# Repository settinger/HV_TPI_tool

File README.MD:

# High-Voltage Tiny Programming Interface (HVTPI) Tool

For an upcoming project I needed a way to use the High-Voltage Tiny Programming Interface (HVTPI) protocol. If you're at all familiar with the High-Voltage Serial Programming (HVSP) that can be used on most ATmegas and ATtinys that use the SPI protocol, then you would be justified to assume HVTPI is a convoluted process dissimilar from standard TPI. But, mercifully, that is not the case! HVTPI is just TPI, but instead of pulling the <span style="text-decoration:overline">RESET</span> pin LOW, you pull it up to 12V.

Two low-cost options for TPI programming are the [USBasp](https://www.fischl.de/usbasp/) (with the [latest firmware](https://blog.podkalicki.com/how-to-update-avr-usbasp-firmware-to-latest-version/)) or the [TPI Programming Arduino Sketch](http://junkplusarduino.blogspot.com/p/attiny10-resources.html) by Junk+Arduino and others. Neither the USBasp nor the Arduino has a pin available to output 12V, of course. That requires some extra hardware.

The task is easy to summarize. Create a new signal that produces 5V when <span style="text-decoration:overline">RESET</span> produces 5V, and goes to 12V when <span style="text-decoration:overline">RESET</span> goes to 0V. On YouTube, [fVripple made a very good one with an optoisolator and a benchtop power supply](https://www.youtube.com/watch?v=7YJOtHbnNDQ), but I wanted to stick to parts I had on-hand and make it more portable. This is what I came up with:

An AP3012 boost converter gives us 12V all the time. While <span style="text-decoration:overline">RESET</span> is HIGH, the forward voltage of the Zener diode is high enough that no current flows through the PNP BJT and the output is equal to <span style="text-decoration:overline">RESET</span>. When <span style="text-decoration:overline">RESET</span> goes LOW, current flows through the 9.1V Zener diode, driving the output to 12V. The 5kΩ resistor value is not a precise one; I think I used 3.3kΩ in practice. And I broke out the 12V signal in case I ever wanted to use it for something else, I dunno what though.

To actually use this schematic, I made two designs: one to go with the USBasp and one to go with the Arduino TPI programmer. I was very sleep-deprived and made some silly design choices.

## The USBasp HVTPI tool

The USBasp HVTPI tool mates nicely with its 2×5 IDC headers. There are two SPDT switches, one to switch between normal TPI and HVTPI modes, and another to combine the two data lines as described in [this application note](http://ww1.microchip.com/downloads/en/AppNotes/doc8373.pdf):

These resistors are not always necessary, which is why they can be disconnected with the switch. The USBasp expects a circuit with a programming pinout like this:

Consequently, the line that is normally labelled "MOSI" acts as the bidirectional line when the USBasp does TPI stuff. This becomes a problem if you are using a circuit that was designed for the [Atmel-ICE](https://ww1.microchip.com/downloads/en/DeviceDoc/Atmel-ICE_UserGuide.pdf), which expects a programming pinout like this:

Both configurations are handled equally well by the 220Ω-resistor switch.

Using the HVTPI tool is as easy as normal TPI. As far as your computer is concerned, there is no difference between this and a normal TPI setup, so no instructions or makefiles have to change.

## The Arduino HVTPI tool

The Arduino-compatible programmer is designed to sit in a breadboard. I originally designed it very skinny, with the HVRST line sticking up like so:

This is not very helpful, so later I went back and put it in a more reasonable 10-DIP layout. Because the Arduino program expects both MISO and MOSI lines to connect to the TPI DATA line via 220Ω resistors, I built that into this board as well. Again, there is no need to make any changes to the normal TPI programming workflow. I know the Arduino sketch has some "HVP" options available, but with this board they are wholly unnecessary.

I'm happily using these with both the USBasp and the Arduino for HVTPI programming. I had a hard time finding good resources for HVTPI and had to do a lot of learning-by-doing, but hopefully I can pass that knowledge along and save someone some trouble.

# Note to self

After setting the ATtiny4/5/9/10/20/40 fuse bits to `0xFE` (or whatever) to enable 12V reset, avrdude can't just overwrite the fuses with `0xFF`. Using the flags `-x section_config -e` will clear the bits.

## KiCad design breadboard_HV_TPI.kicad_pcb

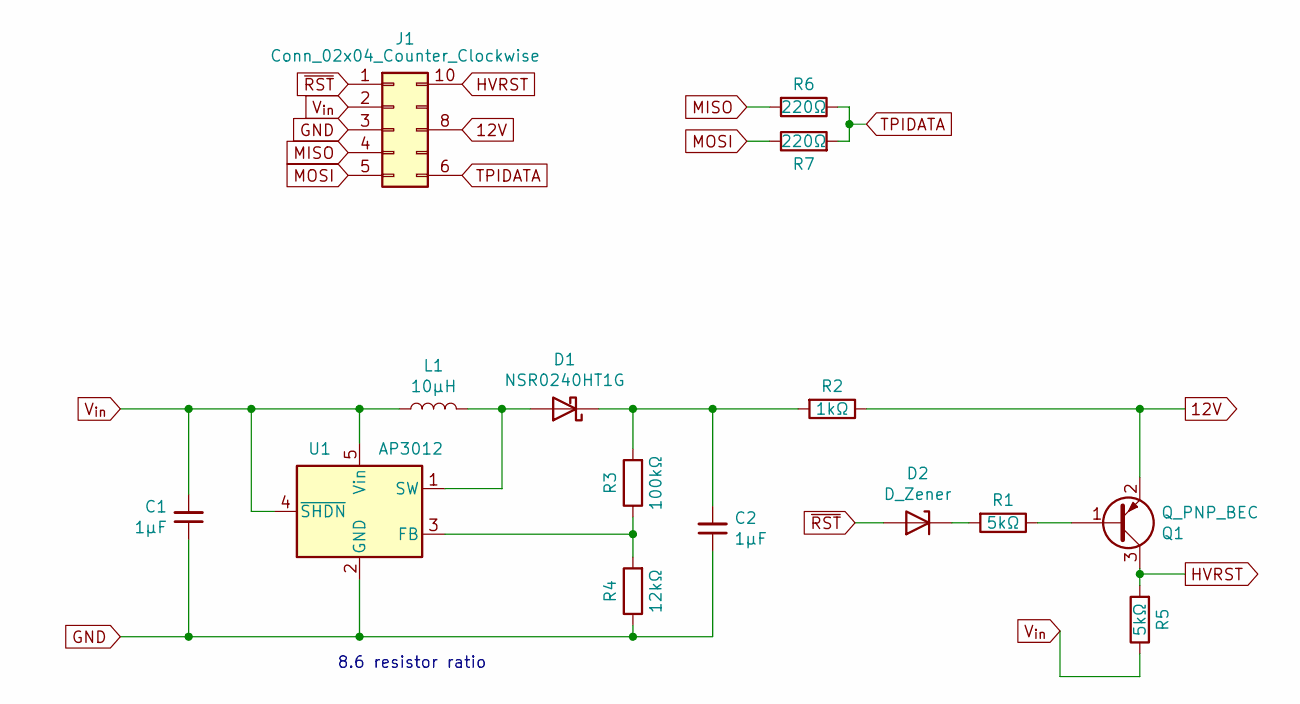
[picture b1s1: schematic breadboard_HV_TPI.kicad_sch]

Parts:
C1, C2: 1μF; C_0805_2012Metric
D1: NSR0240HT1G; D_SOD-323
D2: D_Zener; D_MiniMELF
J1: Conn_02x04_Counter_Clockwise; DIP-10_W7.62mm
L1: 10μH; L_0805_2012Metric
Q1: Q_PNP_BEC; SOT-23
R1, R5: 5kΩ; R_0805_2012Metric
R2: 1kΩ; R_0805_2012Metric
R3: 100kΩ; R_0805_2012Metric
R4: 12kΩ; R_0805_2012Metric
R6, R7: 220Ω; R_0805_2012Metric
U1: AP3012; SOT-23-5

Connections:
12V: J1.8, Q1.2 (E), R2.1
GND: C1.1, C2.1, J1.3, R4.1, U1.2 (GND)
HVRST: J1.10, Q1.3 (C), R5.2
MISO: J1.4, R6.2
MOSI: J1.5, R7.1
unnamed: C2.2, D1.1 (K), R2.2, R3.2
unnamed: D1.2 (A), L1.2, U1.1 (SW)
unnamed: D2.1 (K), R1.2
unnamed: Q1.1 (B), R1.1
unnamed: R3.1, R4.2, U1.3 (FB)
TPIDATA: J1.6, R6.1, R7.2
V_{in}: C1.2, J1.2, L1.1, R5.1, U1.4 (~SHDN), U1.5 (Vin)
~RST: D2.2 (A), J1.1

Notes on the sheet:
8.6 resistor ratio

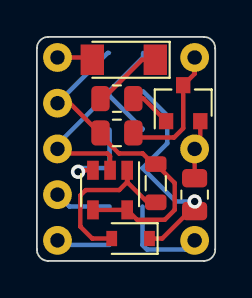
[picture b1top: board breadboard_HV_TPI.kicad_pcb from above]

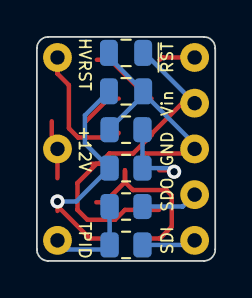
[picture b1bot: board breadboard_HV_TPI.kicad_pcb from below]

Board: 2 copper layers, 9.9 x 12.4 mm, 15 parts (6 on the bottom side), 13 nets.

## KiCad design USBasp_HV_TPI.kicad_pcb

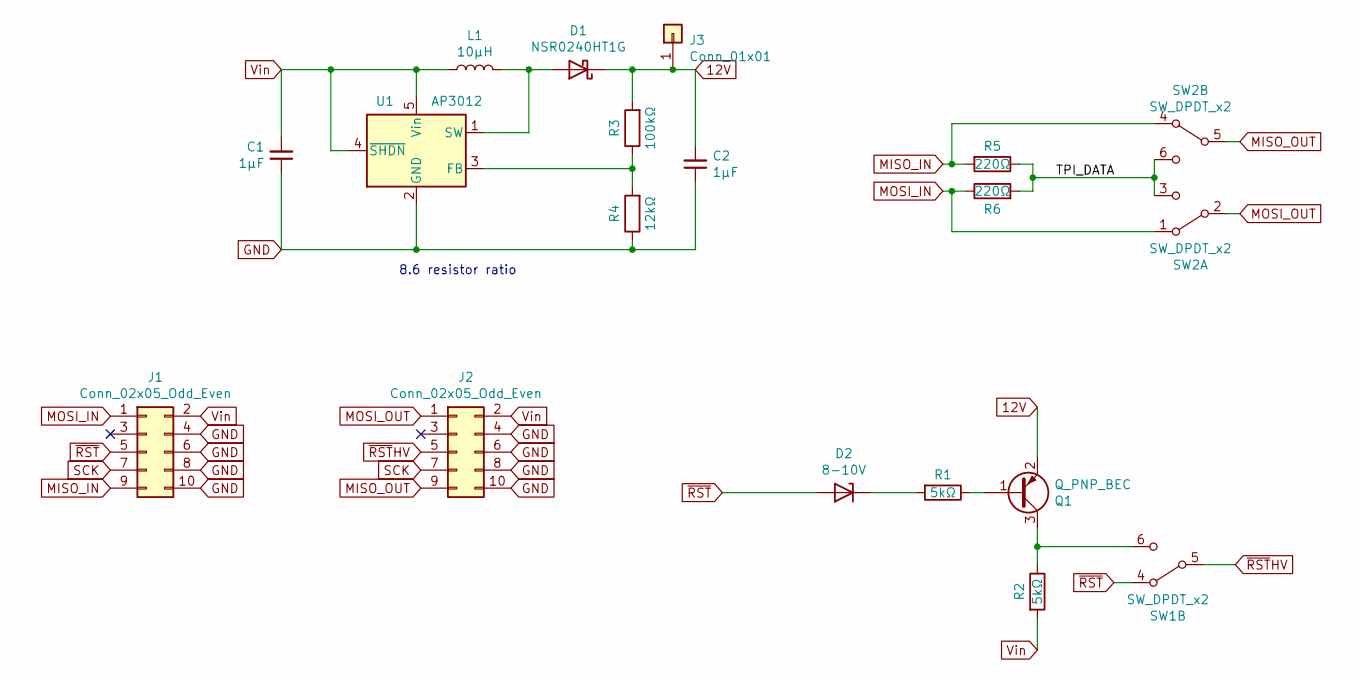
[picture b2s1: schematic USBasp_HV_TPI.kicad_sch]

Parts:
C1, C2: 1μF; C_0805_2012Metric
D1: NSR0240HT1G; D_SOD-323
D2: 8-10V; D_MiniMELF
J1: Conn_02x05_Odd_Even; IDC_Socket_2x05_P2.54mm_edge-mount
J2: Conn_02x05_Odd_Even; IDC_Header_2x05_P2.54mm_edge-mount
J3: Conn_01x01; PinHeader_1x01_P2.54mm_Vertical
L1: 10μH; L_0805_2012Metric
Q1: Q_PNP_BEC; SOT-23
R1, R2: 5kΩ; R_0805_2012Metric
R3: 100kΩ; R_0805_2012Metric
R4: 12kΩ; R_0805_2012Metric
R5, R6: 220Ω; R_0805_2012Metric
SW1, SW2: SW_DPDT_x2; SW_CuK_JS202011CQN_DPDT_Straight
U1: AP3012; SOT-23-5

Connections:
12V: C2.2, D1.1 (K), J3.1, Q1.2 (E), R3.2
/TPI_DATA: R5.1, R6.2, SW2.3 (C), SW2.6 (C)
GND: C1.1, C2.1, J1.4, J1.6, J1.8, J1.10, J2.4, J2.6, J2.8, J2.10, R4.1, U1.2 (GND)
MISO_IN: J1.9, R5.2, SW2.4 (A)
MISO_OUT: J2.9, SW2.5 (B)
MOSI_IN: J1.1, R6.1, SW2.1 (A)
MOSI_OUT: J2.1, SW2.2 (B)
unnamed: D1.2 (A), L1.2, U1.1 (SW)
unnamed: D2.1 (K), R1.2
unnamed: Q1.1 (B), R1.1
unnamed: Q1.3 (C), R2.1, SW1.6 (C)
unnamed: R3.1, R4.2, U1.3 (FB)
SCK: J1.7, J2.7
Vin: C1.2, J1.2, J2.2, L1.1, R2.2, U1.4 (~SHDN), U1.5 (Vin)
~RST: D2.2 (A), J1.5, SW1.4 (A)
~RSTHV: J2.5, SW1.5 (B)

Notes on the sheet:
8.6 resistor ratio

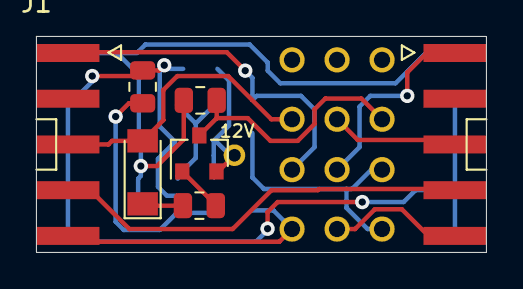
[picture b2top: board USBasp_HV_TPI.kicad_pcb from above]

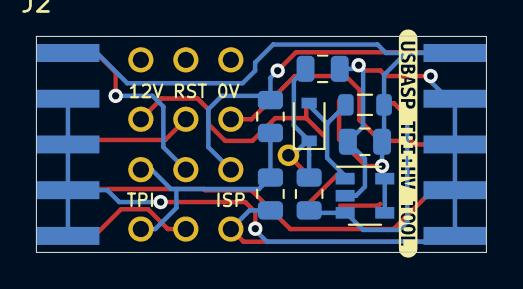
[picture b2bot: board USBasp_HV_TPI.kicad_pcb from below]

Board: 2 copper layers, 25.0 x 12.0 mm, 19 parts (11 on the bottom side), 16 nets.

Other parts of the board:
svg2mod: G***; label

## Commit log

2022-02-14 First commit very sleepy
2022-02-14 minor readme tweak
